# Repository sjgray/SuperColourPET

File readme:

SuperColourPET
==============

Introduction
------------

This is a project to create a Commodore SuperPET compatible computer with Colour. My ColourPET project aimed to add colour to a standard PET computer. While successful, ultimately I determined that adding all the features I wanted, like 80 column mode and graphics, would require too much hacking of a PET motherboard to be practical. So, I moved on to other projects. Recently I worked on the CLCD recreation project which provided the foundation for a nice 80 column 16-colour RGBI video using a 8563 VDC chip. This chip also supports graphics and software-defined fonts. I've also been interested in the dual-CPU SuperPET, with a 6809 CPU. So naturally I thought why not combine these things together? The result is the SuperColourPET (SCP). On top of that I wanted to go one more step to add a Z80 CPU for CP/M capabilities.

Recently there has been interest in PET replacement boards fitting in standard PET cases and talk of also putting them in C64 cases. Why not both? So I've come up with a single board design that will fit in PET, C64 (breadbin), and 64C cases. When installed in a PET case all three ports on the back will be the same as a regular PET board. The 2nd cassette port will be available on a header. When installed in a C64-type case it provides access to a C64 compatible audio/video port, semi-compatible C64 cartridge port, IEC port, power, and two configurable joystick ports. The board only takes up 2/3 of the C64 case and the C64 cassette and user-port cutouts will be free. I will be designing different boards that can be mounted here for access to PET cassette and USER port, or to IEEE and RGBI port etc. All the ports on the board have headers so you can select which ports you want to extend out those two openings.

Status
------

2023-02-24 - Prototype design complete. PCB's have been made. Project is on hold.
2024-01-04 - Github created. Posted Kicad design files.

*** The PROTO board has not been populated nor verified as working!!!!!
*** No CPLD code is written. Firmware is in planning stage.
*** This project should be considered as PRE-ALPHA! Use at own risk. Design subject to change!!!!!!!!!!!!!!!

That being said, much of the design is derived from my Commodore CLCD design, which is at the stage of basic
operation. The PET circuitry is based on the standard PET design. I am planning to build this bit-by-bit
starting with PET functionality and slowly adding the other CPU's over time. This is a long-term project!

Steve

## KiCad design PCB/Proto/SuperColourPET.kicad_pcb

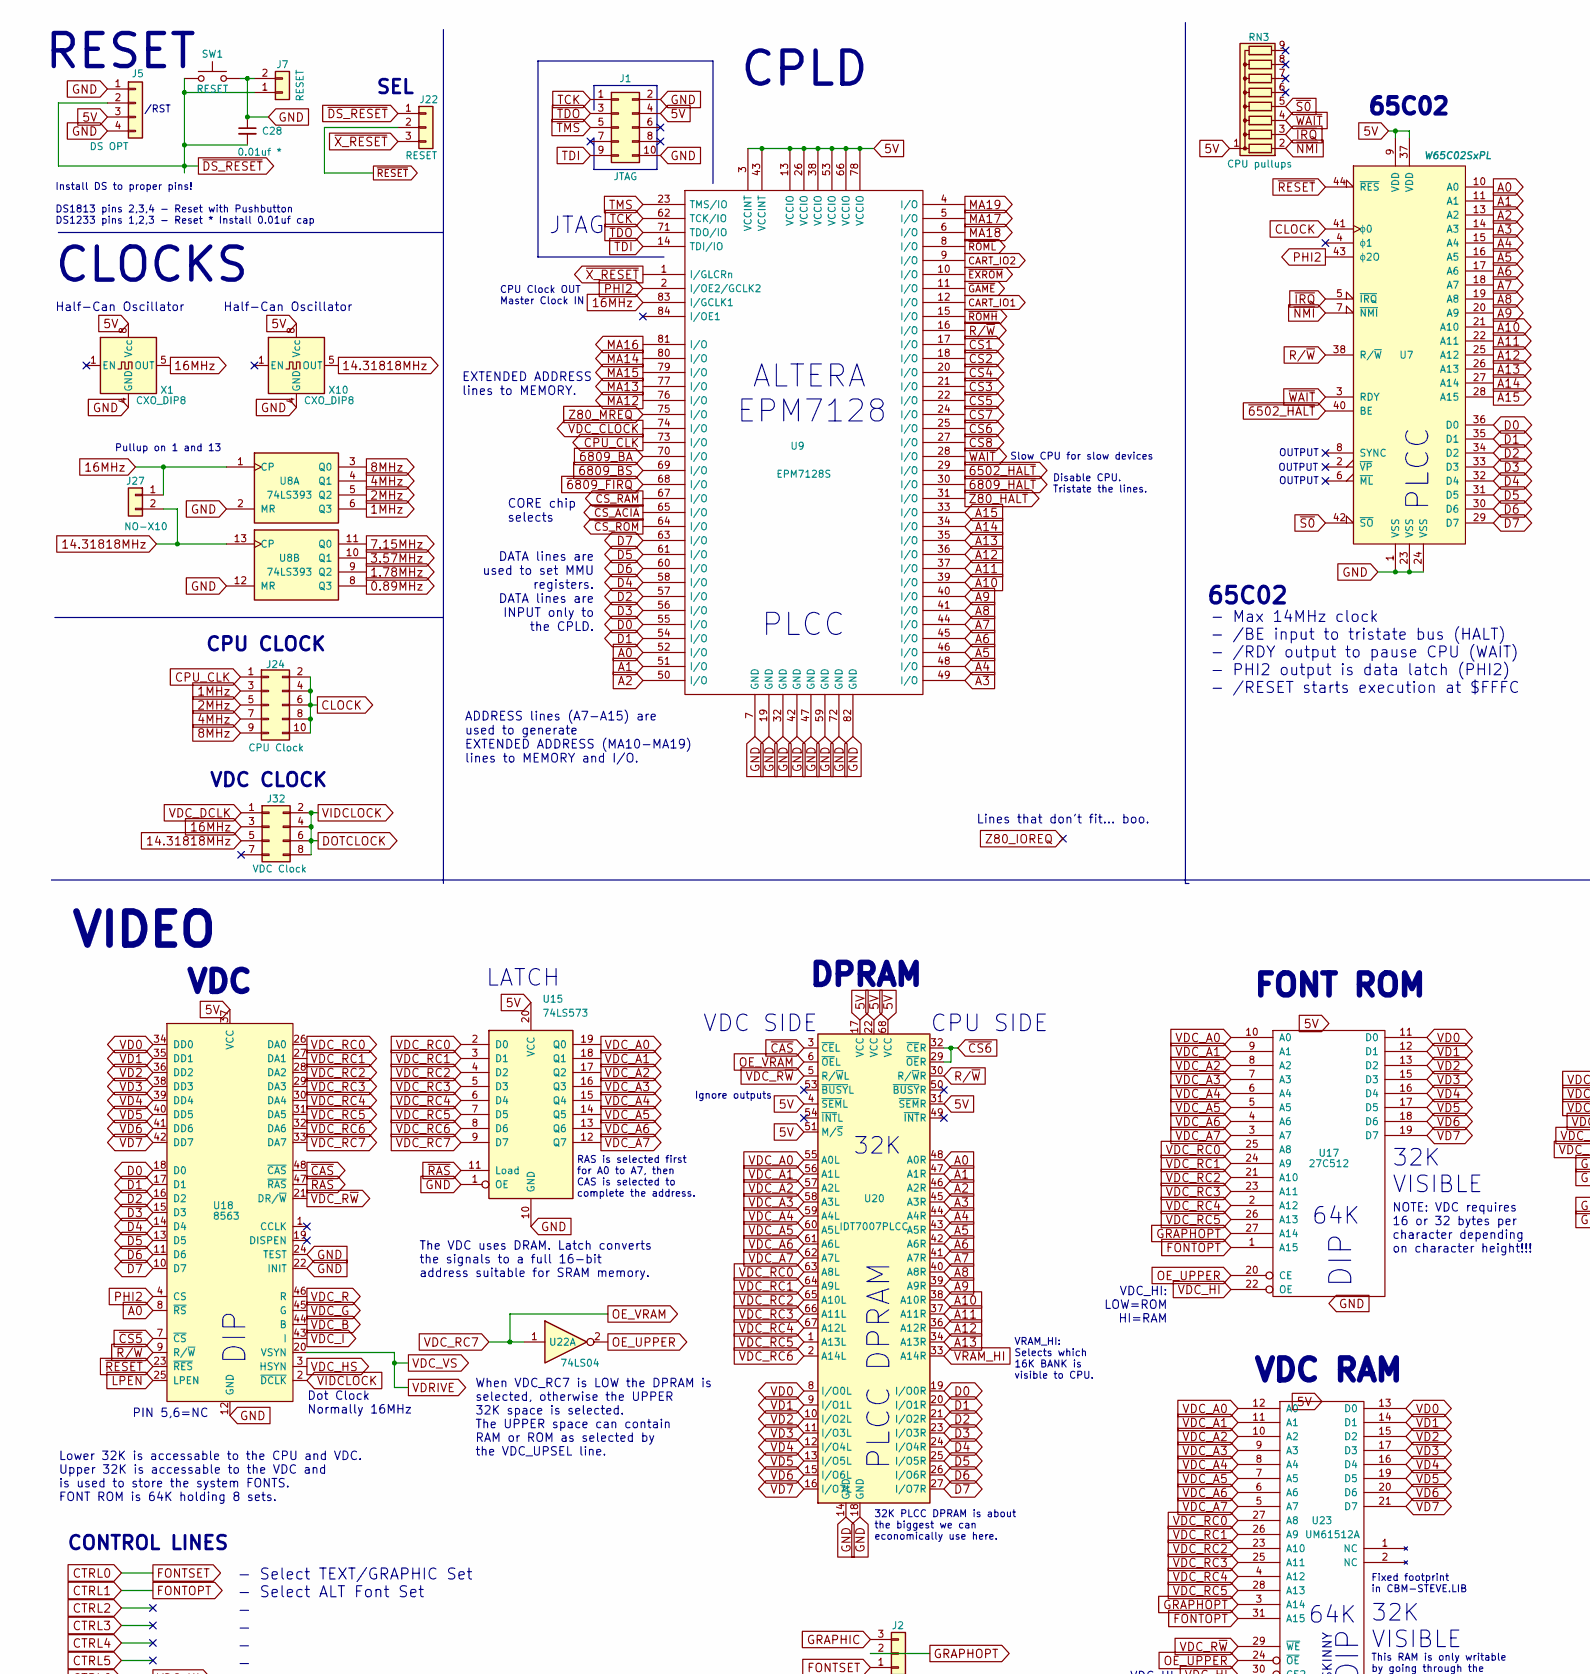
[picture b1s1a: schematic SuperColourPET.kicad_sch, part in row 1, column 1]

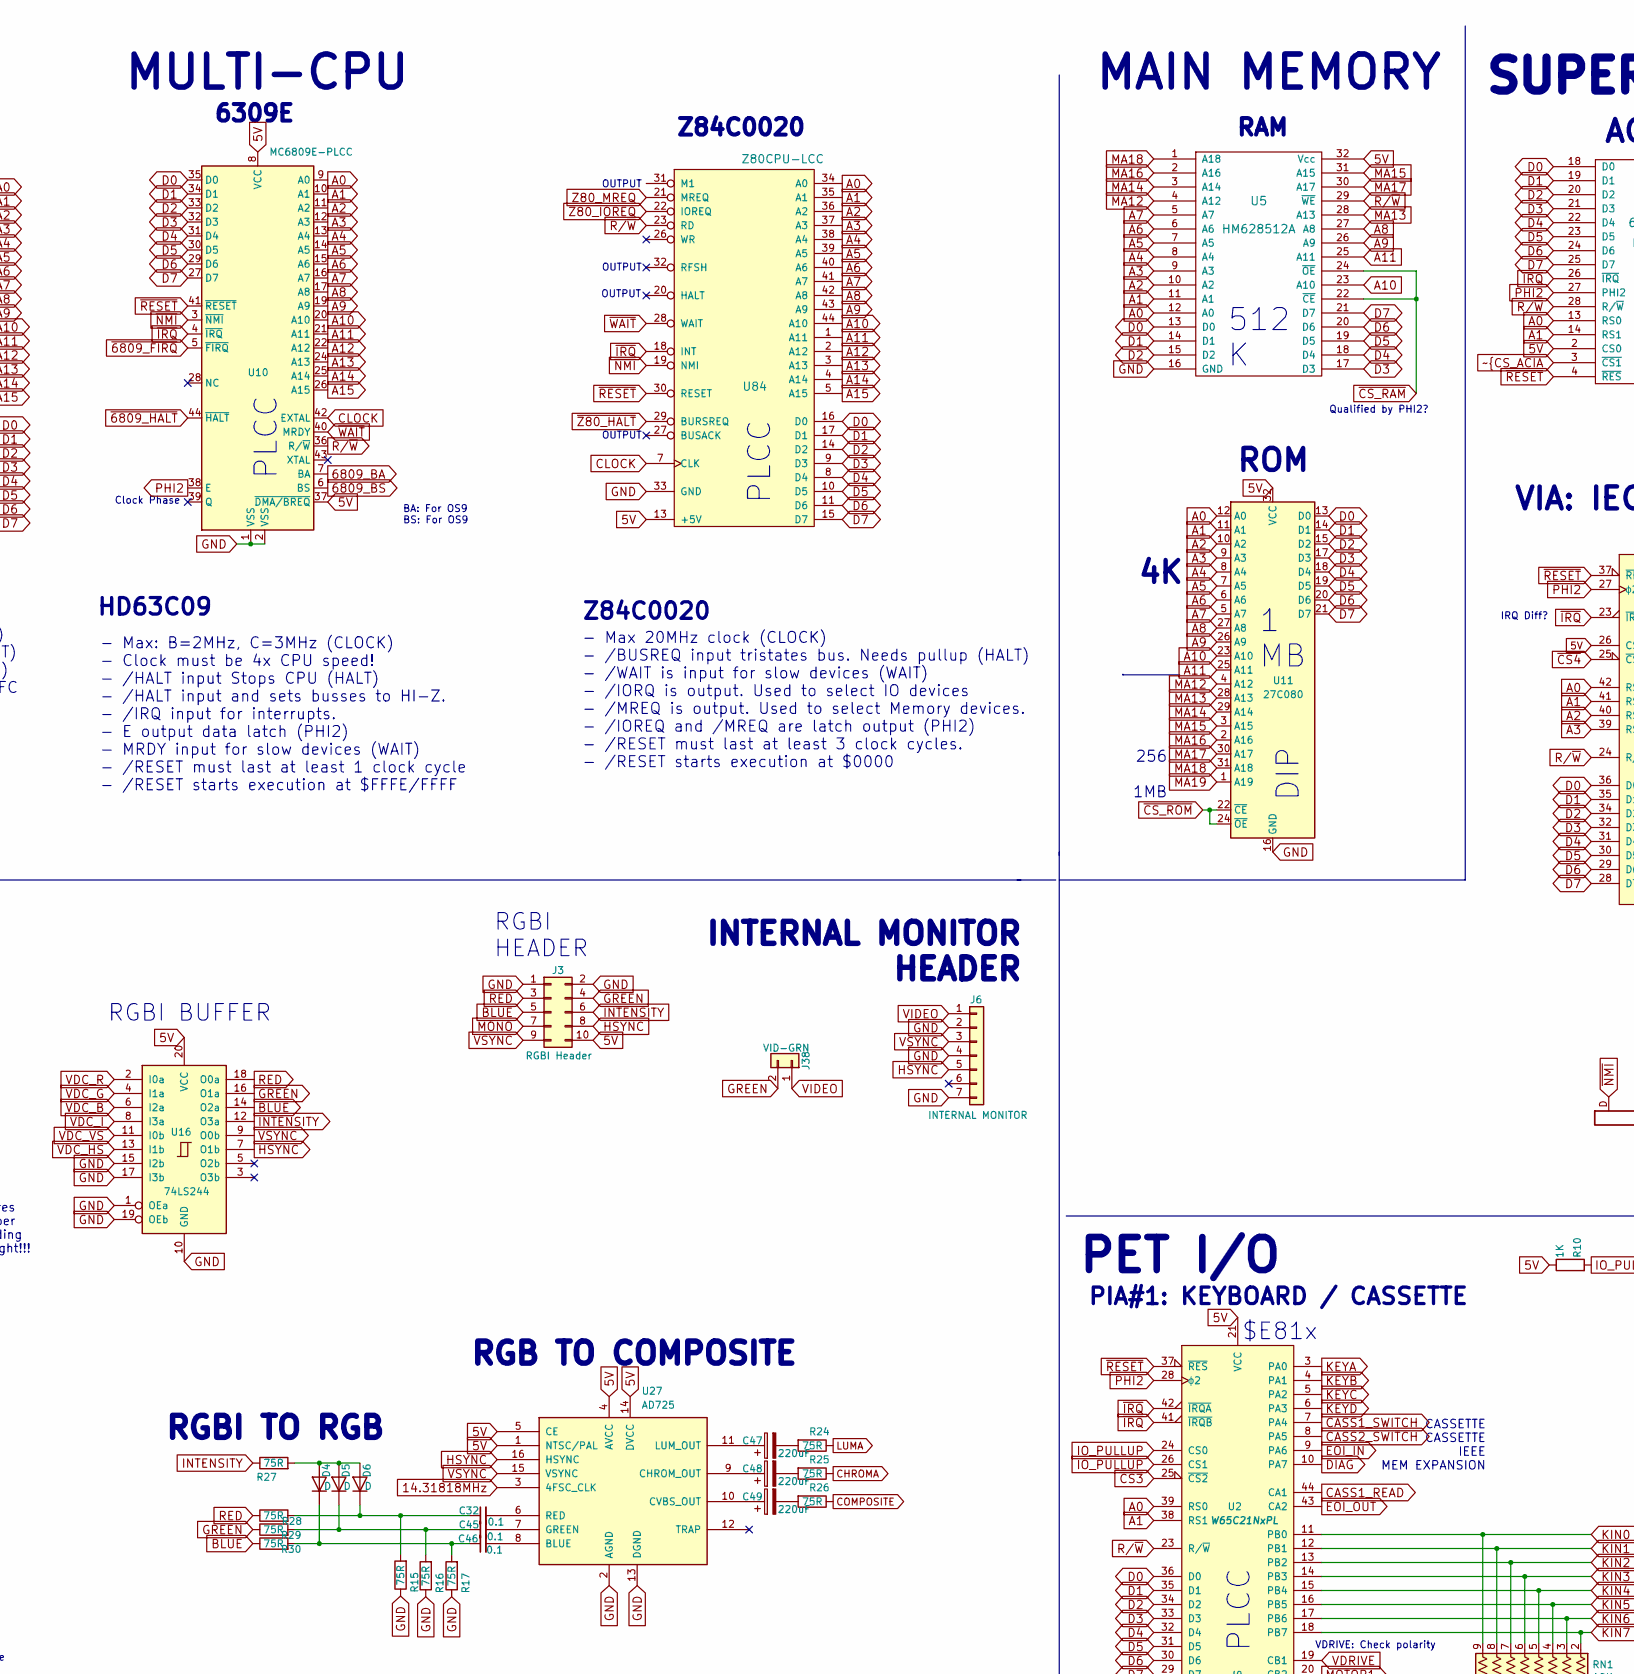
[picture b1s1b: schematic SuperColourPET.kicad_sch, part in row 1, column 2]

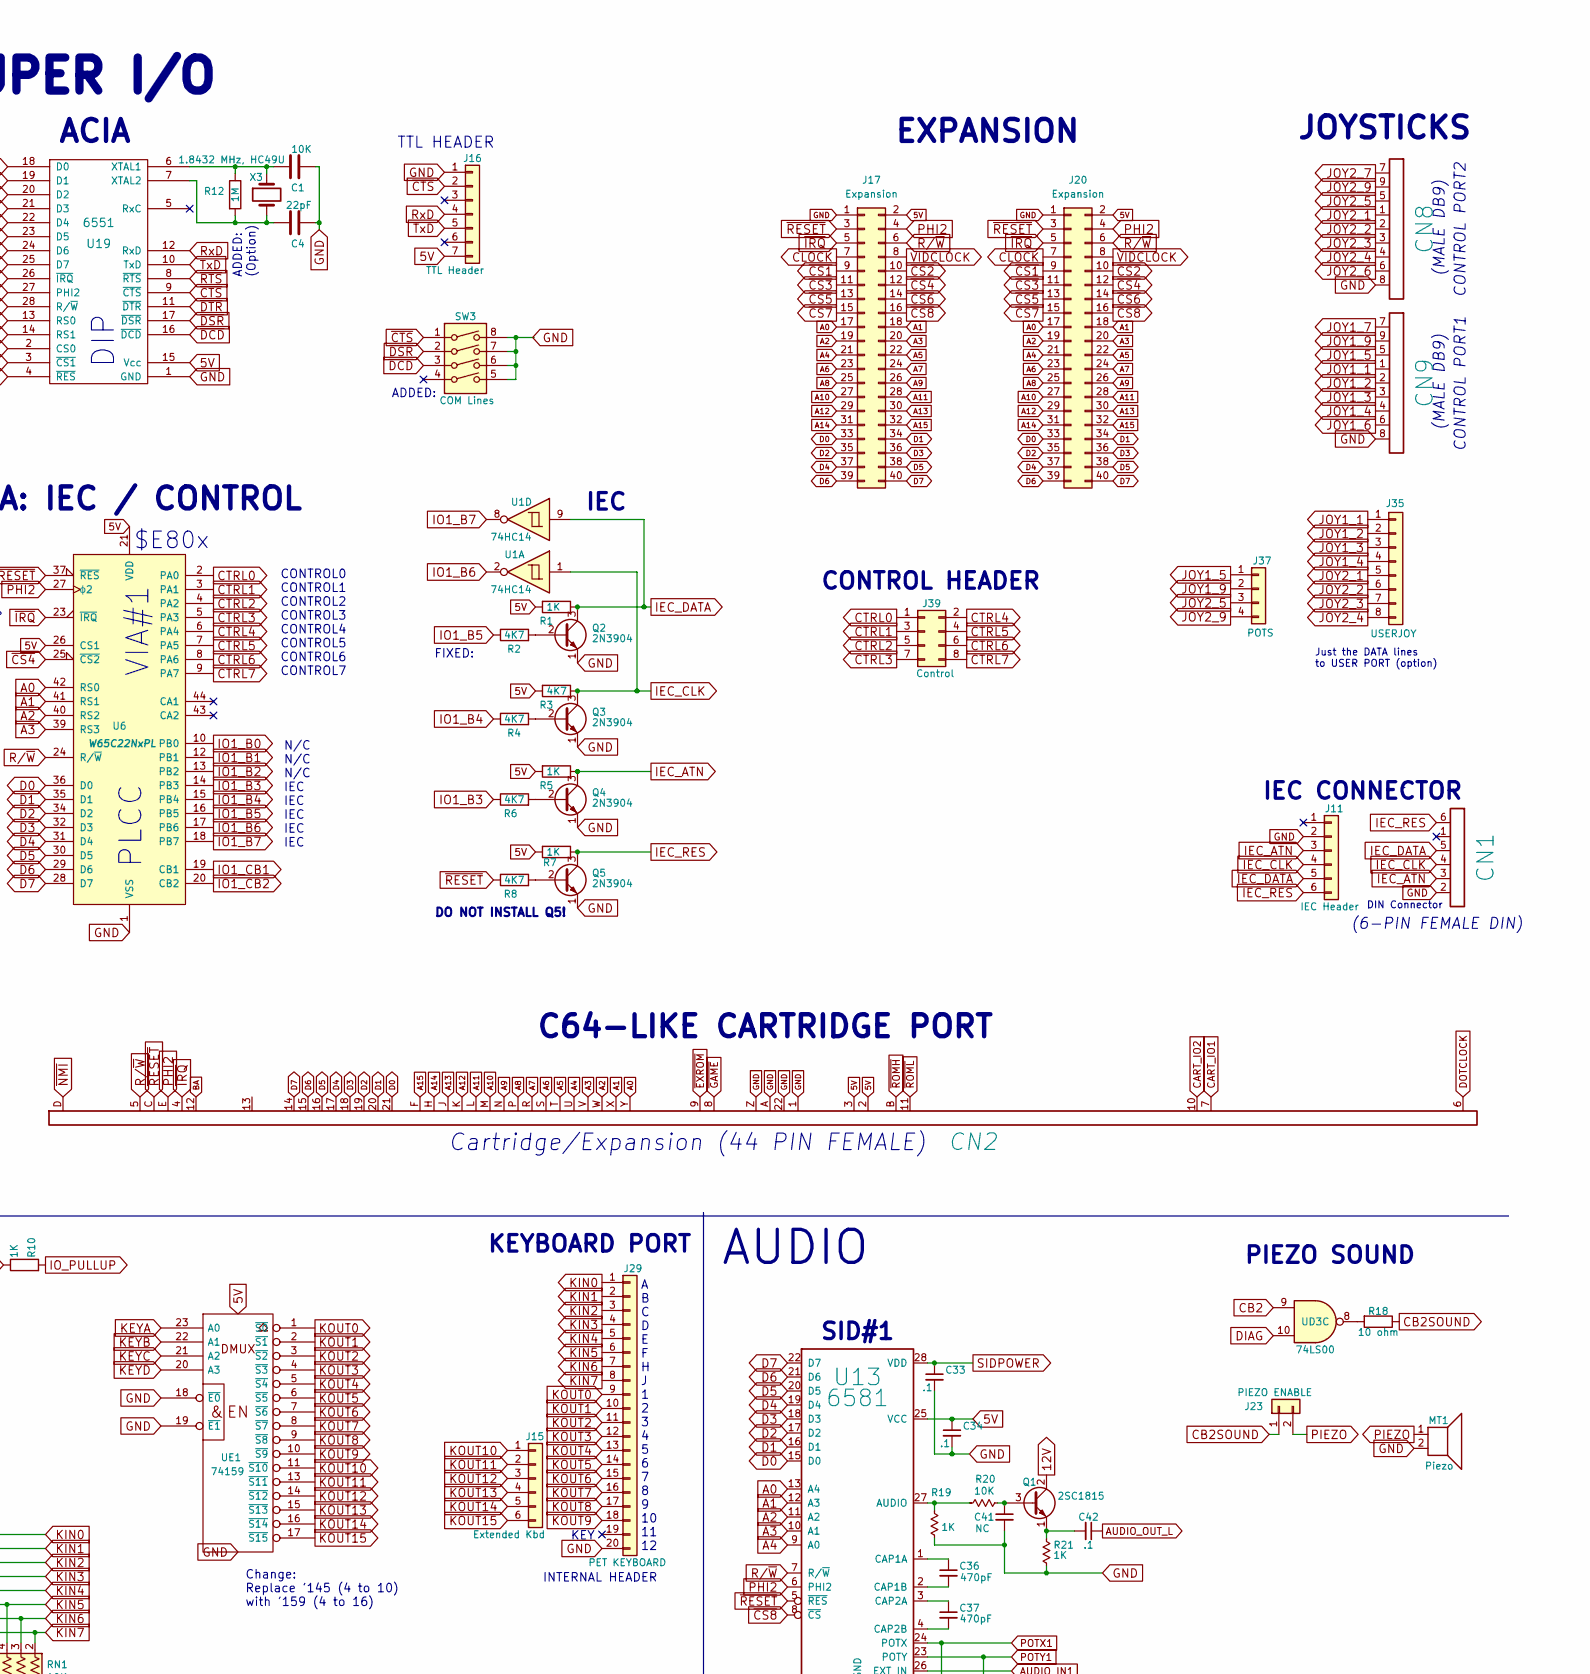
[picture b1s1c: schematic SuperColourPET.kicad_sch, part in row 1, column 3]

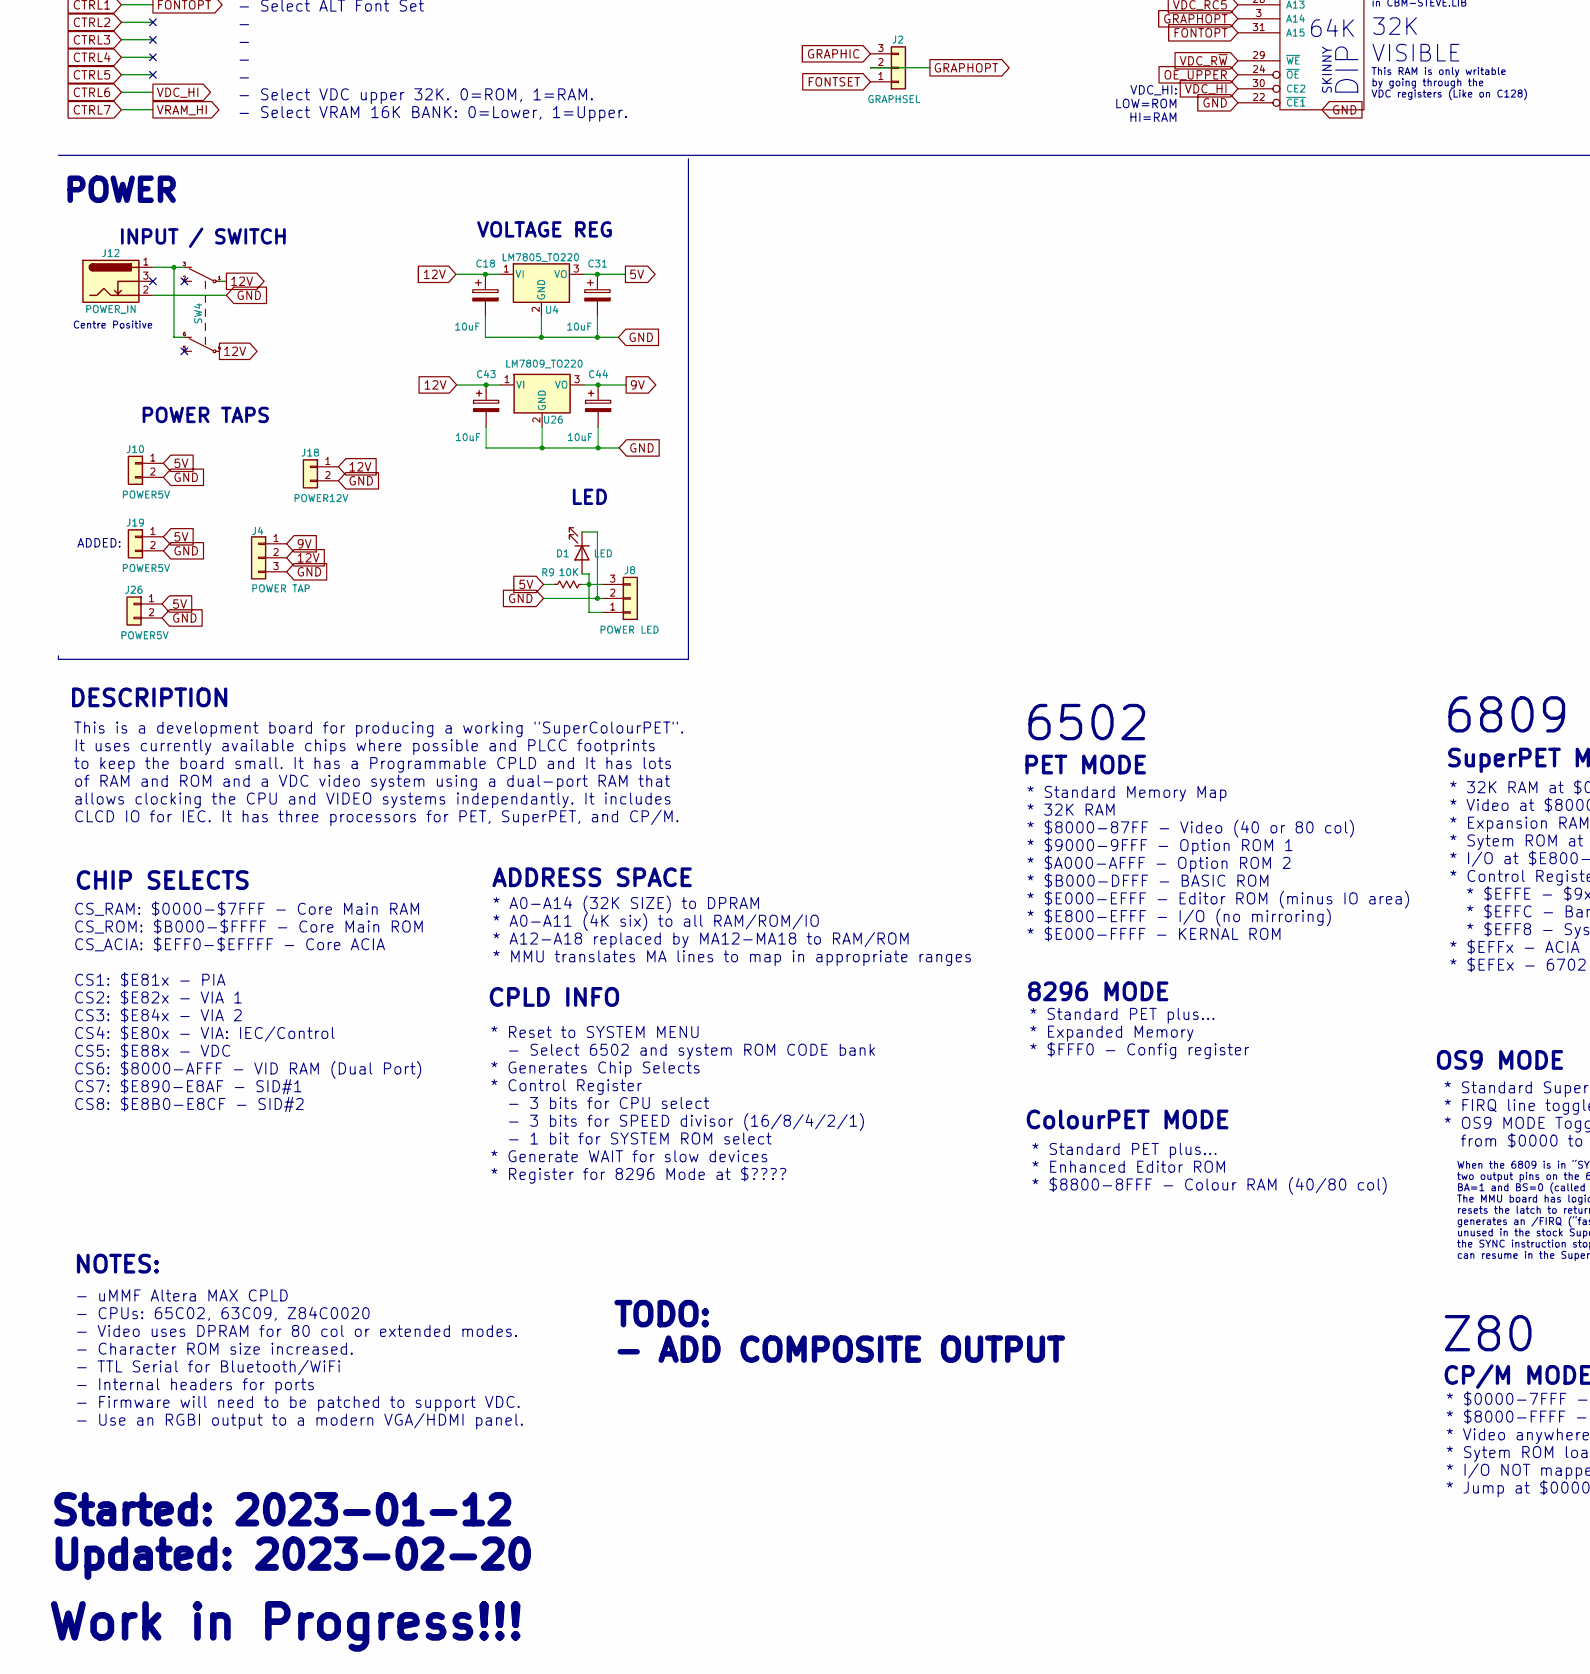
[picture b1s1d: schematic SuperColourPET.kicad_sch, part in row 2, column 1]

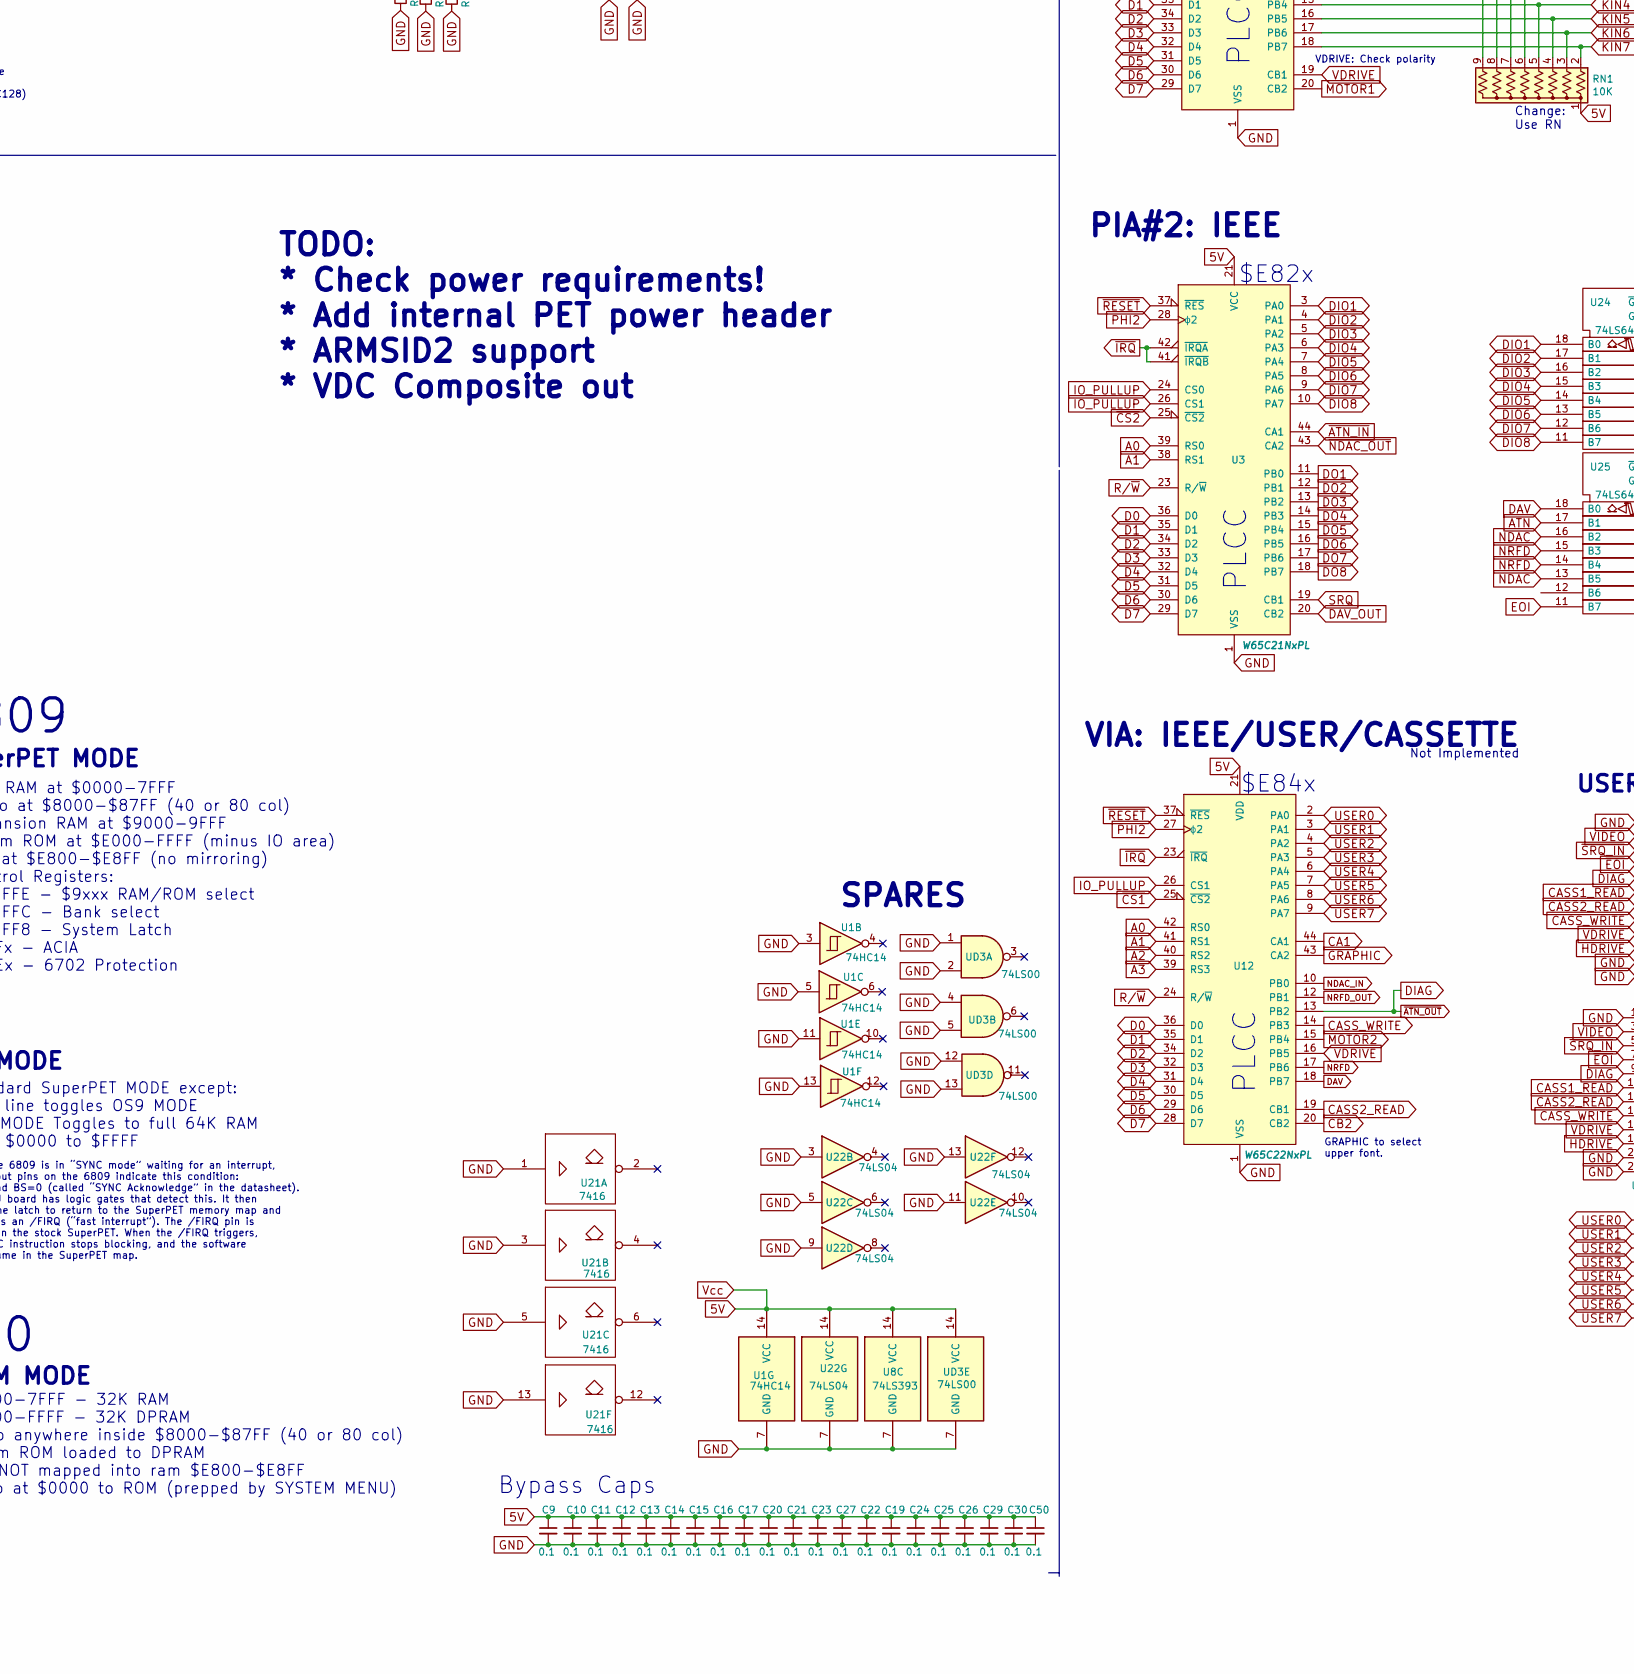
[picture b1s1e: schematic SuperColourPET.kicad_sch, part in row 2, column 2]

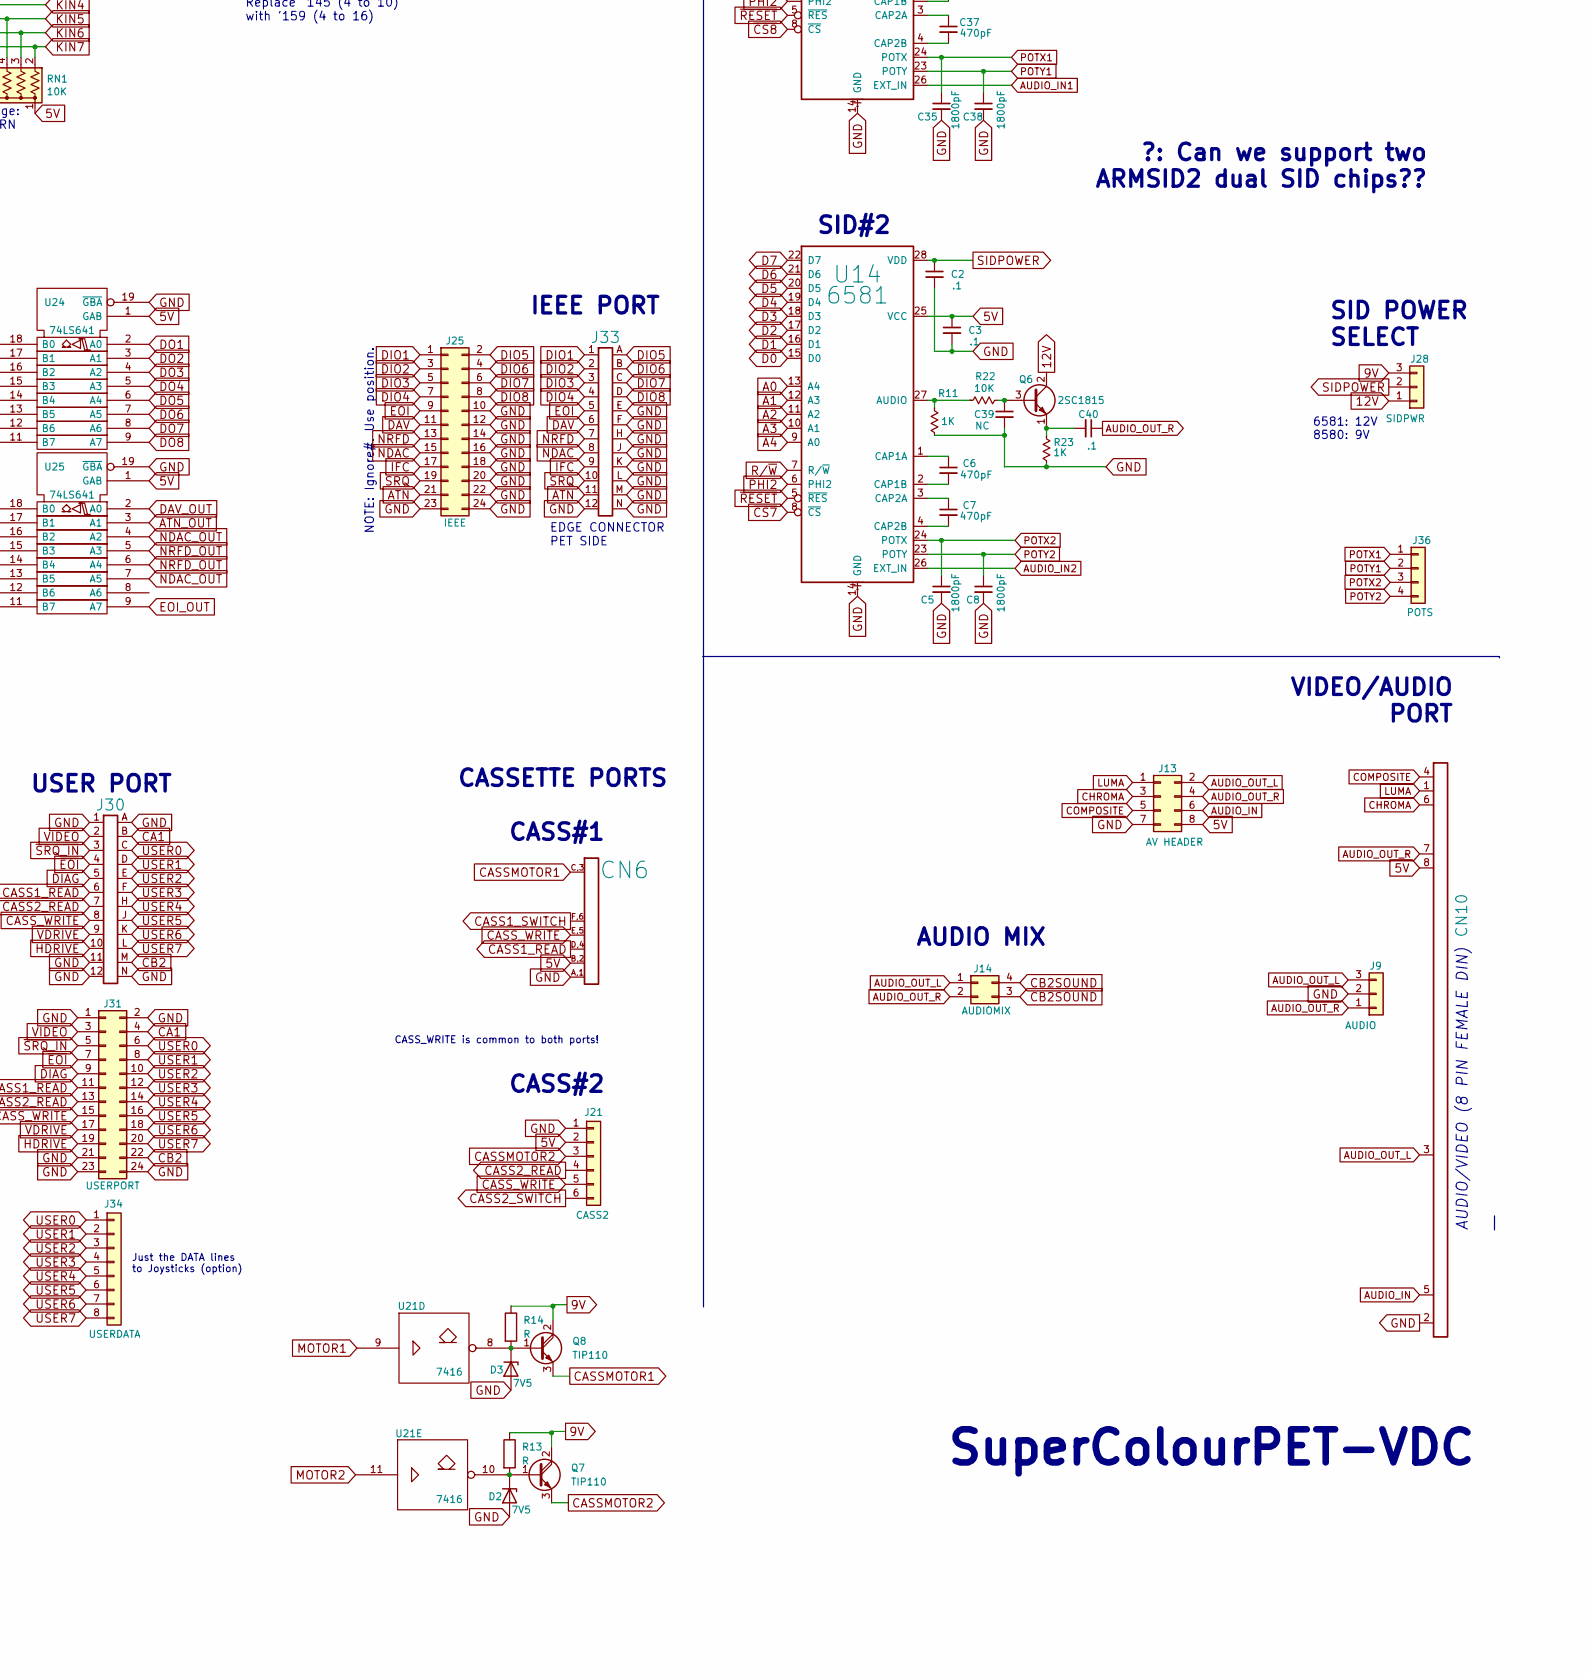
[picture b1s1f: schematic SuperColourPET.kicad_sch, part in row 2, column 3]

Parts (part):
C1: 10K; C_Disc_D4.7mm_W2.5mm_P5.00mm
C2, C3, C33, C34, C40, C42: .1; C_Disc_D4.7mm_W2.5mm_P5.00mm
C4: 22pF; C_Disc_D4.7mm_W2.5mm_P5.00mm
C5, C8, C35, C38: 1800pF; C_Disc_D4.7mm_W2.5mm_P5.00mm
C6, C7, C36, C37: 470pF; C_Disc_D4.7mm_W2.5mm_P5.00mm
C9, C10, C11, C12, C13, C14, C15, C16, C17, C19, C20, C21, C22, C23, C24, C25, C26, C27, C29, C30, C32, C45, C46, C50: 0.1; C_Disc_D4.7mm_W2.5mm_P5.00mm
C18, C31, C43, C44: 10uF; CP_Radial_D7.5mm_P2.50mm
C28: 0.01uf *; C_Disc_D4.7mm_W2.5mm_P5.00mm
C39, C41: NC; C_Disc_D4.7mm_W2.5mm_P5.00mm
C47, C48, C49: 220uF; CP_Radial_D4.0mm_P1.50mm
CN1: SERIAL_BUS_CON; SERIAL_CON_DIN6
CN2: EXPANSION_PORT
CN6: CASS1; EDGE_CON_12P_TAPE
CN8, CN9: CONTROL_PORT; JOYPORT_DB9
CN10: AV_CONN; AV_CON_DIN8
D1: LED; LED_D3.0mm
D2, D3: 7V5; D_A-405_P10.16mm_Horizontal
D4, D5, D6: D; D_A-405_P2.54mm_Vertical_AnodeUp
J1: JTAG; PinHeader_2x05_P2.54mm_Vertical
J2: GRAPHSEL; PinHeader_1x03_P2.54mm_Vertical
J3: RGBI Header; PinHeader_2x05_P2.54mm_Vertical
J4: POWER TAP; PinHeader_1x03_P2.54mm_Vertical
J5: DS OPT; PinHeader_1x04_P2.54mm_Vertical
J6: INTERNAL MONITOR; PinHeader_1x07_P2.54mm_Vertical
J7: RESET; PinHeader_1x02_P2.54mm_Vertical
J8: POWER LED; PinHeader_1x03_P2.54mm_Vertical
J9: AUDIO; PinHeader_1x03_P2.54mm_Vertical
J10, J19, J26: POWER5V; PinHeader_1x02_P2.54mm_Vertical
J11: IEC Header; PinHeader_1x06_P2.54mm_Vertical
J12: POWER_IN; BarrelJack_Horizontal
J13: AV HEADER; PinHeader_2x04_P2.54mm_Vertical
J14: AUDIOMIX; PinHeader_2x02_P2.54mm_Vertical
J15: Extended Kbd; PinHeader_1x06_P2.54mm_Vertical
J16: TTL Header; PinHeader_1x07_P2.54mm_Vertical
J17, J20: Expansion; PinHeader_2x20_P2.54mm_Vertical
J18: POWER12V; PinHeader_1x02_P2.54mm_Vertical
J21: CASS2; PinHeader_1x06_P2.54mm_Vertical
J22: RESET; PinHeader_1x03_P2.54mm_Vertical
J23: PIEZO ENABLE; PinHeader_1x02_P2.54mm_Vertical
J24: CPU Clock; PinHeader_2x05_P2.54mm_Vertical
J25: IEEE; PinHeader_2x12_P2.54mm_Vertical
J27: NO-X10; PinHeader_1x02_P2.54mm_Vertical
J28: SIDPWR; PinHeader_1x03_P2.54mm_Vertical
J29: PET KEYBOARD; PinHeader_1x20_P2.54mm_Vertical
J30: USERPORT; EDGE_CON_24P
J31: USERPORT; PinHeader_2x12_P2.54mm_Vertical
J32: VDC Clock; PinHeader_2x04_P2.54mm_Vertical
J33: IEEE; EDGE_CON_24P
J34: USERDATA; PinHeader_1x08_P2.54mm_Vertical
J35: USERJOY; PinHeader_1x08_P2.54mm_Vertical
J36, J37: POTS; PinHeader_1x04_P2.54mm_Vertical
J38: VID-GRN; PinHeader_1x02_P2.54mm_Vertical
J39: Control; PinHeader_2x04_P2.54mm_Vertical
MT1: Piezo; TestPoint_2Pads_Pitch2.54mm_Drill0.8mm
Q1, Q6: 2SC1815; TO-92_Inline_Wide
Q2, Q3, Q4, Q5: 2N3904; TO-92_Inline_Wide
Q7, Q8: TIP110; TO-220-3_Vertical
R1, R5, R7: 1K; R_Axial_DIN0207_L6.3mm_D2.5mm_P2.54mm_Vertical
R2, R3, R4, R6, R8: 4K7; R_Axial_DIN0207_L6.3mm_D2.5mm_P2.54mm_Vertical
R9, R20, R22: 10K; R_Axial_DIN0204_L3.6mm_D1.6mm_P7.62mm_Horizontal
R10, R11, R19, R21, R23: 1K; R_Axial_DIN0204_L3.6mm_D1.6mm_P7.62mm_Horizontal
R12: 1M; R_Axial_DIN0204_L3.6mm_D1.6mm_P7.62mm_Horizontal
R13, R14: R; R_Axial_DIN0204_L3.6mm_D1.6mm_P7.62mm_Horizontal
R15, R16, R17, R24, R25, R26, R27, R28, R29, R30: 75R; R_Axial_DIN0207_L6.3mm_D2.5mm_P2.54mm_Vertical
R18: 10 ohm; R_Axial_DIN0204_L3.6mm_D1.6mm_P7.62mm_Horizontal
RN1: 10K; R_Array_SIP9
RN3: CPU pullups; R_Array_SIP9
SW1: RESET; SW_Tactile_SPST_Angled_PTS645Vx58-2LFS
SW3: COM Lines; SW_DIP_SPSTx04_Slide_9.78x12.34mm_W7.62mm_P2.54mm
SW4: POWER_SWITCH
U1: 74HC14
U2, U3: W65C21NxPL; PLCC-44_THT-Socket
U4: LM7805_TO220; TO-220-3_Vertical
U5: HM628512A; DIP-32_W15.24mm_LongPads
U6, U12: W65C22NxPL; PLCC-44_THT-Socket
U7: W65C02SxPL; PLCC-44_THT-Socket
U8: 74LS393; DIP-14_W7.62mm_LongPads
U9: EPM7128S; PLCC-84_THT-Socket
U10: MC6809E-PLCC; PLCC-44_THT-Socket
U11: 27C080; DIP-32_W15.24mm_LongPads
U13, U14: 6581; DIP-28_W15.24mm_LongPads
U15: 74LS573; DIP-20_W7.62mm_LongPads
U16: 74LS244; DIP-20_W7.62mm_LongPads
U17: 27C512; DIP-28_W15.24mm_LongPads
U18: 8563; DIP-48_W15.24mm_LongPads
U19: 6551; DIP-28_W15.24mm_LongPads
U20: IDT7007PLCC; PLCC-68_THT-Socket
U21: 7416; DIP-14_W7.62mm_LongPads
U22: 74LS04; DIP-14_W7.62mm_LongPads
U23: UM61512A; DIP-32_W7.62mm
U24, U25: 74LS641; DIP-20_W7.62mm_LongPads
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
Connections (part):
0.89MHz: U8.8 (Q3)
1.78MHz: U8.9 (Q2)
1MHz: J24.3, U8.6 (Q3)
2MHz: J24.5, U8.5 (Q2)
3.57MHz: U8.10 (Q1)
4MHz: J24.7, U8.4 (Q1)
5V: C3.1, C9.1, C10.1, C11.1, C12.1, C13.1, C14.1, C15.1, C16.1, C17.1, C19.1, C20.1, C21.1, C22.1, C23.1, C24.1, C25.1, C26.1, C27.1, C29.1, C30.1, C31.1, C34.1, C50.1, CN2.2, CN2.3, CN6.B,2, CN10.8, J1.4, J3.10, J5.3, J10.1, J13.8, J16.7, J17.2, J19.1, J20.2, J21.2, J26.1, R1.2, R3.2, R5.2, R7.2, R9.2, R10.1, RN1.1 (common), RN3.1 (common), U1.14 (VCC), U2.21 (VCC), U3.21 (VCC), U4.3 (VO), U5.32 (Vcc), U6.21 (VDD), U6.26 (CS1), U7.9 (VDD), U7.37 (VDD), U8.14 (VCC), U9.3 (VCCINT), U9.13 (VCCIO), U9.26 (VCCIO), U9.38 (VCCIO), U9.43 (VCCINT), U9.53 (VCCIO), U9.66 (VCCIO), U9.78 (VCCIO), U10.8 (VCC), U10.37 (~DMA/BREQ), U11.32 (VCC), U12.21 (VDD), U13.25 (VCC), U14.25 (VCC), U15.20 (VCC), U16.20 (VCC), U17.28 (VCC), U18.37 (VCC), U19.2 (CS0), U19.15 (Vcc), U20.4 (~SEML), U20.17 (VCC), U20.22 (VCC), U20.31 (~SEMR)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
7.15MHz: U8.11 (Q0)
8MHz: J24.9, U8.3 (Q0)
9V: C44.1, J4.1, J28.3, Q7.2 (C), Q8.2 (C), R13.1, R14.1, U26.3 (VO)
12V: C18.1, C43.1, J4.2, J18.1, J28.1, Q1.2 (C), Q6.2 (C), SW4.1, SW4.4, U4.1 (VI), U26.1 (VI)
14.31818MHz: J27.2, J32.5, U8.13 (CP), U27.3 (4FSC_CLK), X10.5 (OUT)
16MHz: J27.1, J32.3, U8.1 (CP), U9.83 (I/GCLK1), X1.5 (OUT)
6809_BA: U9.70 (I/O), U10.7 (BA)
6809_BS: U9.69 (I/O), U10.6 (BS)
A0: CN2.Y, J17.17, J20.17, U2.39 (RS0), U3.39 (RS0), U5.12 (A0), U6.42 (RS0), U7.10 (A0), U9.52 (I/O), U10.9 (A0), U11.12 (A0), U12.42 (RS0), U13.13 (A4), U14.13 (A4), U18.8 (~RS), U19.13 (RS0), U20.48 (A0R), U84.34 (A0)
A1: CN2.X, J17.18, J20.18, U2.38 (RS1), U3.38 (RS1), U5.11 (A1), U6.41 (RS1), U7.11 (A1), U9.51 (I/O), U10.10 (A1), U11.11 (A1), U12.41 (RS1), U13.12 (A3), U14.12 (A3), U19.14 (RS1), U20.47 (A1R), U84.35 (A1)
A2: CN2.W, J17.19, J20.19, U5.10 (A2), U6.40 (RS2), U7.13 (A2), U9.50 (I/O), U10.11 (A2), U11.10 (A2), U12.40 (RS2), U13.11 (A2), U14.11 (A2), U20.46 (A2R), U84.36 (A2)
A3: CN2.V, J17.20, J20.20, U5.9 (A3), U6.39 (RS3), U7.14 (A3), U9.49 (I/O), U10.12 (A3), U11.9 (A3), U12.39 (RS3), U13.10 (A1), U14.10 (A1), U20.45 (A3R), U84.37 (A3)
A4: CN2.U, J17.21, J20.21, U5.8 (A4), U7.15 (A4), U9.48 (I/O), U10.13 (A4), U11.8 (A4), U13.9 (A0), U14.9 (A0), U20.44 (A4R), U84.38 (A4)
A5: CN2.T, J17.22, J20.22, U5.7 (A5), U7.16 (A5), U9.46 (I/O), U10.14 (A5), U11.7 (A5), U20.43 (A5R), U84.39 (A5)
A6: CN2.S, J17.23, J20.23, U5.6 (A6), U7.17 (A6), U9.45 (I/O), U10.15 (A6), U11.6 (A6), U20.42 (A6R), U84.40 (A6)
A7: CN2.R, J17.24, J20.24, U5.5 (A7), U7.18 (A7), U9.44 (I/O), U10.16 (A7), U11.5 (A7), U20.41 (A7R), U84.41 (A7)
A8: CN2.P, J17.25, J20.25, U5.27 (A8), U7.19 (A8), U9.41 (I/O), U10.17 (A8), U11.27 (A8), U20.40 (A8R), U84.42 (A8)
A9: CN2.N, J17.26, J20.26, U5.26 (A9), U7.20 (A9), U9.40 (I/O), U10.19 (A9), U11.26 (A9), U20.39 (A9R), U84.43 (A9)
A10: CN2.M, J17.27, J20.27, U5.23 (A10), U7.21 (A10), U9.39 (I/O), U10.20 (A10), U11.23 (A10), U20.38 (A10R), U84.44 (A10)
A11: CN2.L, J17.28, J20.28, U5.25 (A11), U7.22 (A11), U9.37 (I/O), U10.21 (A11), U11.25 (A11), U20.37 (A11R), U84.1 (A11)
A12: CN2.K, J17.29, J20.29, U7.25 (A12), U9.36 (I/O), U10.22 (A12), U20.36 (A12R), U84.2 (A12)
A13: CN2.J, J17.30, J20.30, U7.26 (A13), U9.35 (I/O), U10.24 (A13), U20.34 (A13R), U84.3 (A13)
A14: CN2.H, J17.31, J20.31, U7.27 (A14), U9.34 (I/O), U10.25 (A14), U84.4 (A14)
A15: CN2.F, J17.32, J20.32, U7.28 (A15), U9.33 (I/O), U10.26 (A15), U84.5 (A15)
ATN: J25.21, J33.11, U25.17 (B1)
ATN_OUT: U25.3 (A1)
AUDIO_IN: CN10.5, J13.6
AUDIO_IN1: U13.26 (EXT_IN)
AUDIO_IN2: U14.26 (EXT_IN)
AUDIO_OUT_L: C42.1, CN10.3, J9.3, J13.2, J14.1
AUDIO_OUT_R: C40.1, CN10.7, J9.1, J13.4, J14.2
BA: CN2.12
BLUE: J3.5, R30.1, U16.14 (O2a)
CA1: J30.B, J31.4, U12.44 (CA1)
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
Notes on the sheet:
GRAPHIC to select upper font.
VDC_HI: LOW=ROM HI=RAM
SEL
* Standard SuperPET MODE except: * FIRQ line toggles OS9 MODE * OS9 MODE Toggles to full 64K RAM from $0000 to $FFFF
6502
6581: 12V 8580: 9V
This is a development board for producing a working "SuperColourPET". It uses currently available chips where possible and PLCC footprints to keep the board small. It has a Programmable CPLD and It has lots of RAM and ROM and a VDC video system using a dual-port RAM that allows clocking the CPU and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
CHIP SELECTS
SUPER I/O
* Standard Memory Map * 32K RAM * $8000-87FF - Video (40 or 80 col) * $9000-9FFF - Option ROM 1 * $A000-AFFF - Option ROM 2 * $B000-DFFF - BASIC ROM * $E000-EFFF - Editor ROM (minus IO area) * $E800-EFFF - I/O (no mirroring) * $E000-FFFF - KERNAL ROM
CONTROL0 CONTROL1 CONTROL2 CONTROL3 CONTROL4 CONTROL5 CONTROL6 CONTROL7
- Max 14MHz clock - /BE input to tristate bus (HALT) - /RDY output to pause CPU (WAIT) - PHI2 output is data latch (PHI2) - /RESET starts execution at $FFFC
IEC
A B C D E F H J 1 2 3 4 5 6 7 8 9 10 11 12
ROM
8296 MODE
TTL HEADER
PLCC
MAIN MEMORY
$E82x
VOLTAGE REG
CASS_WRITE is common to both ports!
?: Can we support two ARMSID2 dual SID chips??
RGBI BUFFER
AUDIO
JTAG
/RST
CPLD
6809
FIXED:
ADDED:
VIA#1
CP/M MODE
NOTE: VDC requires 16 or 32 bytes per character depending on character height!!!
TODO: * Check power requirements! * Add internal PET power header * ARMSID2 support * VDC Composite out
VDC RAM
AUDIO MIX
ColourPET MODE
PIA#2: IEEE
TODO: - ADD COMPOSITE OUTPUT

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
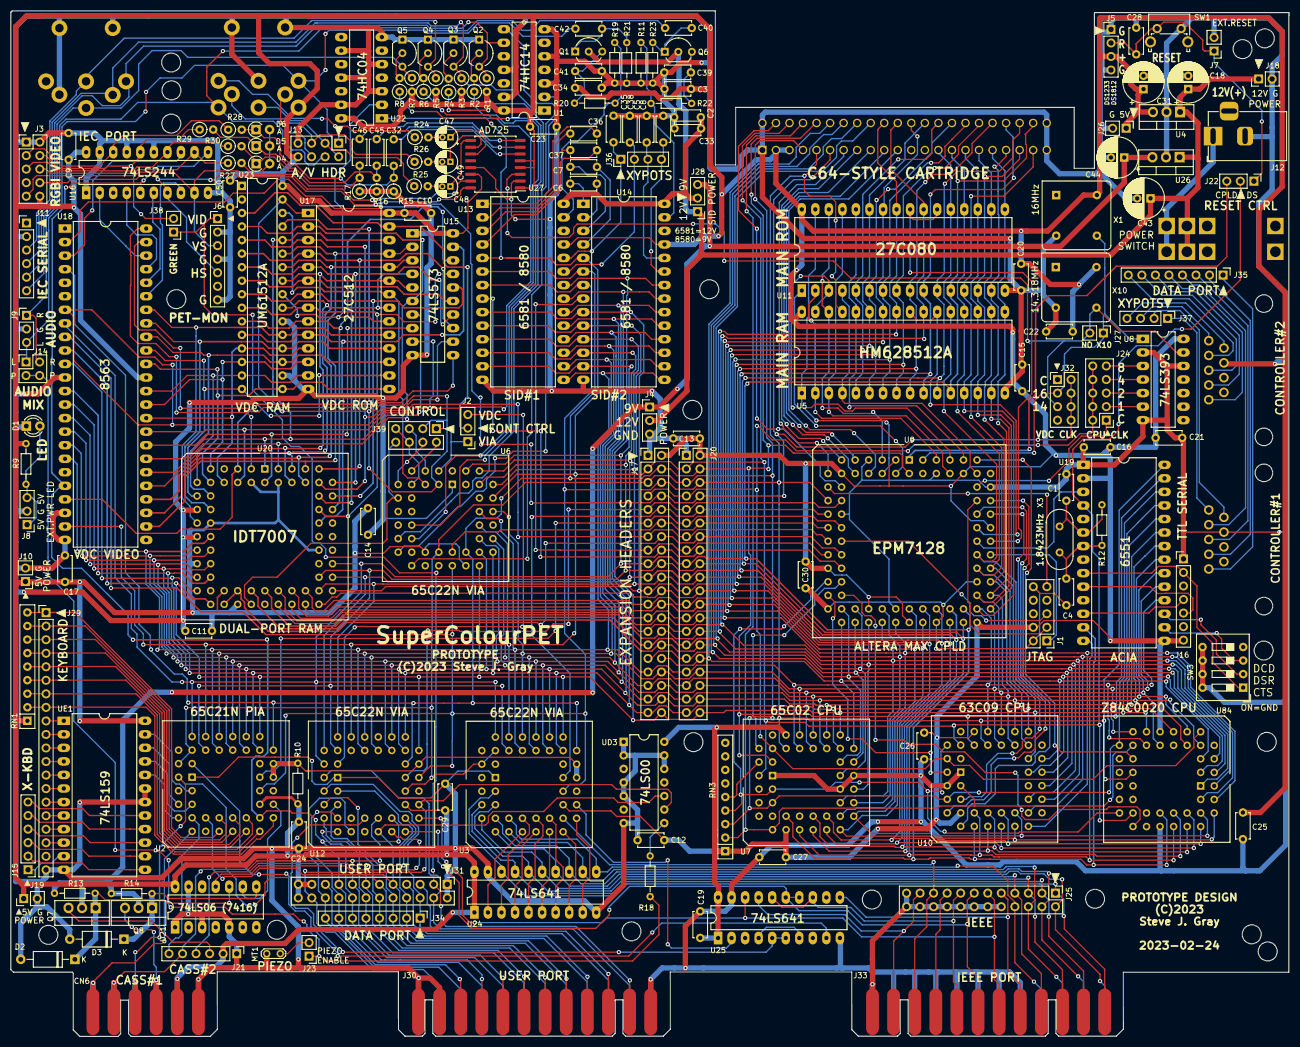
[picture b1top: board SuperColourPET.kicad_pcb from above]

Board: 2 copper layers, 239.8 x 192.4 mm, 178 parts (0 on the bottom side), 289 nets.

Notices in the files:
PCB/Proto/SuperColourPET.kicad_pcb:
(C)2023 Steve J. Gray
(C)2023
